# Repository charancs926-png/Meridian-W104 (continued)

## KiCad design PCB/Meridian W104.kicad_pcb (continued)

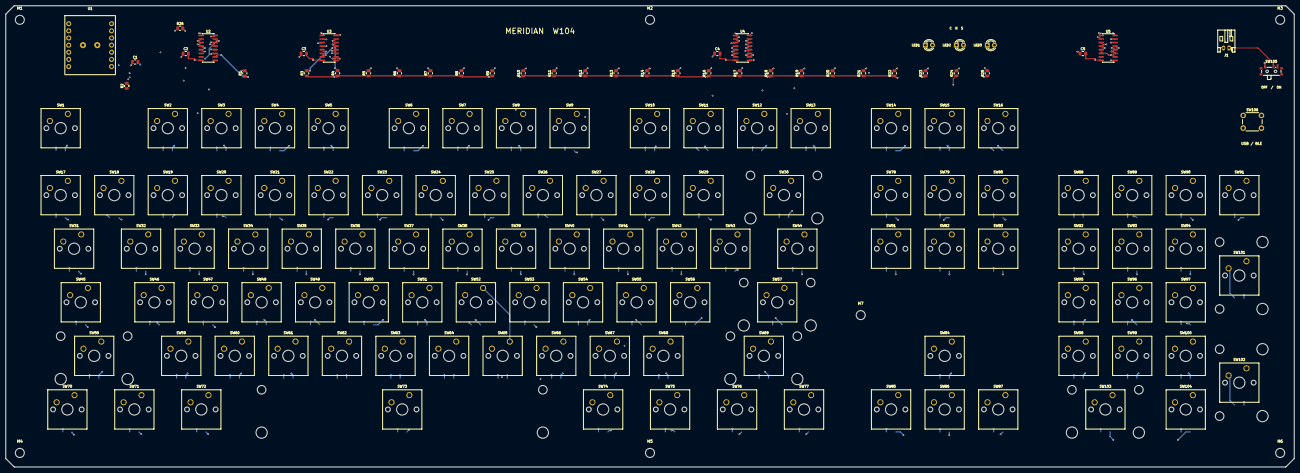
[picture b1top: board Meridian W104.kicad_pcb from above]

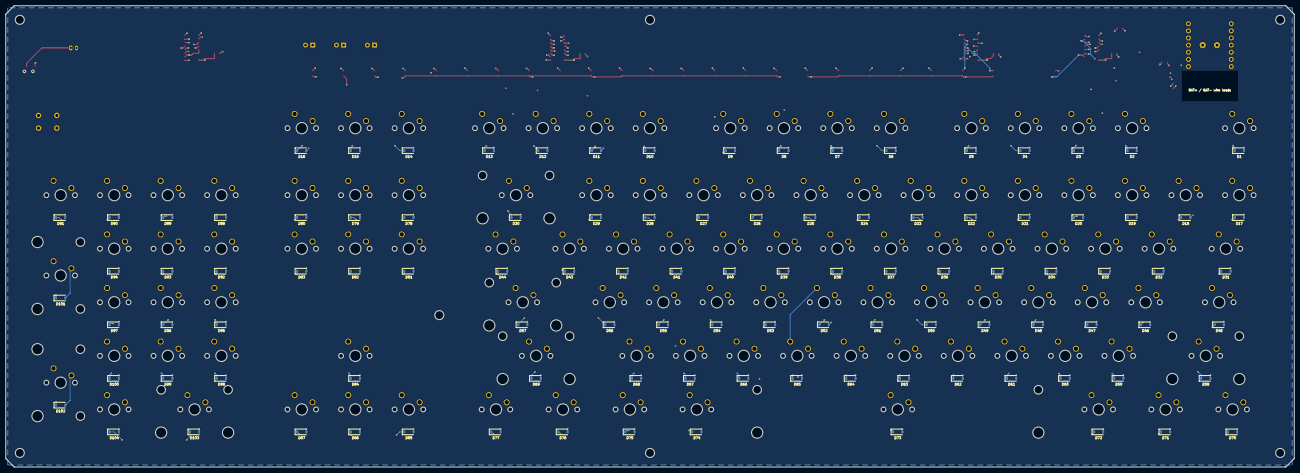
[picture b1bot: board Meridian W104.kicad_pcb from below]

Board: 4 copper layers, 458.1 x 164.0 mm, 257 parts (104 on the bottom side), 152 nets.

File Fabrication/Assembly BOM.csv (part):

Reference,Value,Footprint,Side,Technology,Notes
C1,10u / 10V,Capacitor_SMD:C_0805_2012Metric,Top,SMD,
C2,100n,Capacitor_SMD:C_0805_2012Metric,Top,SMD,
C3,100n,Capacitor_SMD:C_0805_2012Metric,Top,SMD,
C4,100n,Capacitor_SMD:C_0805_2012Metric,Top,SMD,
C5,100n,Capacitor_SMD:C_0805_2012Metric,Top,SMD,
D1,1N4148W,Diode_SMD:D_SOD-123,Bottom,SMD,
D10,1N4148W,Diode_SMD:D_SOD-123,Bottom,SMD,
D100,1N4148W,Diode_SMD:D_SOD-123,Bottom,SMD,
D101,1N4148W,Diode_SMD:D_SOD-123,Bottom,SMD,
D102,1N4148W,Diode_SMD:D_SOD-123,Bottom,SMD,
D103,1N4148W,Diode_SMD:D_SOD-123,Bottom,SMD,
D104,1N4148W,Diode_SMD:D_SOD-123,Bottom,SMD,
D11,1N4148W,Diode_SMD:D_SOD-123,Bottom,SMD,
D12,1N4148W,Diode_SMD:D_SOD-123,Bottom,SMD,
D13,1N4148W,Diode_SMD:D_SOD-123,Bottom,SMD,
D14,1N4148W,Diode_SMD:D_SOD-123,Bottom,SMD,
D15,1N4148W,Diode_SMD:D_SOD-123,Bottom,SMD,
D16,1N4148W,Diode_SMD:D_SOD-123,Bottom,SMD,
D17,1N4148W,Diode_SMD:D_SOD-123,Bottom,SMD,
D18,1N4148W,Diode_SMD:D_SOD-123,Bottom,SMD,
D19,1N4148W,Diode_SMD:D_SOD-123,Bottom,SMD,
D2,1N4148W,Diode_SMD:D_SOD-123,Bottom,SMD,
D20,1N4148W,Diode_SMD:D_SOD-123,Bottom,SMD,
D21,1N4148W,Diode_SMD:D_SOD-123,Bottom,SMD,
D22,1N4148W,Diode_SMD:D_SOD-123,Bottom,SMD,
D23,1N4148W,Diode_SMD:D_SOD-123,Bottom,SMD,
D24,1N4148W,Diode_SMD:D_SOD-123,Bottom,SMD,
D25,1N4148W,Diode_SMD:D_SOD-123,Bottom,SMD,
D26,1N4148W,Diode_SMD:D_SOD-123,Bottom,SMD,
D27,1N4148W,Diode_SMD:D_SOD-123,Bottom,SMD,
D28,1N4148W,Diode_SMD:D_SOD-123,Bottom,SMD,
D29,1N4148W,Diode_SMD:D_SOD-123,Bottom,SMD,
D3,1N4148W,Diode_SMD:D_SOD-123,Bottom,SMD,
D30,1N4148W,Diode_SMD:D_SOD-123,Bottom,SMD,
D31,1N4148W,Diode_SMD:D_SOD-123,Bottom,SMD,
D32,1N4148W,Diode_SMD:D_SOD-123,Bottom,SMD,
D33,1N4148W,Diode_SMD:D_SOD-123,Bottom,SMD,
D34,1N4148W,Diode_SMD:D_SOD-123,Bottom,SMD,
D35,1N4148W,Diode_SMD:D_SOD-123,Bottom,SMD,
D36,1N4148W,Diode_SMD:D_SOD-123,Bottom,SMD,
D37,1N4148W,Diode_SMD:D_SOD-123,Bottom,SMD,
D38,1N4148W,Diode_SMD:D_SOD-123,Bottom,SMD,
D39,1N4148W,Diode_SMD:D_SOD-123,Bottom,SMD,
D4,1N4148W,Diode_SMD:D_SOD-123,Bottom,SMD,
D40,1N4148W,Diode_SMD:D_SOD-123,Bottom,SMD,
D41,1N4148W,Diode_SMD:D_SOD-123,Bottom,SMD,
D42,1N4148W,Diode_SMD:D_SOD-123,Bottom,SMD,
D43,1N4148W,Diode_SMD:D_SOD-123,Bottom,SMD,
D44,1N4148W,Diode_SMD:D_SOD-123,Bottom,SMD,
D45,1N4148W,Diode_SMD:D_SOD-123,Bottom,SMD,
D46,1N4148W,Diode_SMD:D_SOD-123,Bottom,SMD,
D47,1N4148W,Diode_SMD:D_SOD-123,Bottom,SMD,
D48,1N4148W,Diode_SMD:D_SOD-123,Bottom,SMD,
D49,1N4148W,Diode_SMD:D_SOD-123,Bottom,SMD,
D5,1N4148W,Diode_SMD:D_SOD-123,Bottom,SMD,
D50,1N4148W,Diode_SMD:D_SOD-123,Bottom,SMD,
D51,1N4148W,Diode_SMD:D_SOD-123,Bottom,SMD,
D52,1N4148W,Diode_SMD:D_SOD-123,Bottom,SMD,
D53,1N4148W,Diode_SMD:D_SOD-123,Bottom,SMD,
D54,1N4148W,Diode_SMD:D_SOD-123,Bottom,SMD,
D55,1N4148W,Diode_SMD:D_SOD-123,Bottom,SMD,
D56,1N4148W,Diode_SMD:D_SOD-123,Bottom,SMD,
D57,1N4148W,Diode_SMD:D_SOD-123,Bottom,SMD,
D58,1N4148W,Diode_SMD:D_SOD-123,Bottom,SMD,
D59,1N4148W,Diode_SMD:D_SOD-123,Bottom,SMD,
D6,1N4148W,Diode_SMD:D_SOD-123,Bottom,SMD,
D60,1N4148W,Diode_SMD:D_SOD-123,Bottom,SMD,
D61,1N4148W,Diode_SMD:D_SOD-123,Bottom,SMD,
D62,1N4148W,Diode_SMD:D_SOD-123,Bottom,SMD,
D63,1N4148W,Diode_SMD:D_SOD-123,Bottom,SMD,
D64,1N4148W,Diode_SMD:D_SOD-123,Bottom,SMD,
D65,1N4148W,Diode_SMD:D_SOD-123,Bottom,SMD,
D66,1N4148W,Diode_SMD:D_SOD-123,Bottom,SMD,
D67,1N4148W,Diode_SMD:D_SOD-123,Bottom,SMD,
D68,1N4148W,Diode_SMD:D_SOD-123,Bottom,SMD,
D69,1N4148W,Diode_SMD:D_SOD-123,Bottom,SMD,
D7,1N4148W,Diode_SMD:D_SOD-123,Bottom,SMD,
D70,1N4148W,Diode_SMD:D_SOD-123,Bottom,SMD,
D71,1N4148W,Diode_SMD:D_SOD-123,Bottom,SMD,
D72,1N4148W,Diode_SMD:D_SOD-123,Bottom,SMD,
D73,1N4148W,Diode_SMD:D_SOD-123,Bottom,SMD,
D74,1N4148W,Diode_SMD:D_SOD-123,Bottom,SMD,
D75,1N4148W,Diode_SMD:D_SOD-123,Bottom,SMD,
D76,1N4148W,Diode_SMD:D_SOD-123,Bottom,SMD,
D77,1N4148W,Diode_SMD:D_SOD-123,Bottom,SMD,
D78,1N4148W,Diode_SMD:D_SOD-123,Bottom,SMD,
D79,1N4148W,Diode_SMD:D_SOD-123,Bottom,SMD,
D8,1N4148W,Diode_SMD:D_SOD-123,Bottom,SMD,
D80,1N4148W,Diode_SMD:D_SOD-123,Bottom,SMD,
D81,1N4148W,Diode_SMD:D_SOD-123,Bottom,SMD,
D82,1N4148W,Diode_SMD:D_SOD-123,Bottom,SMD,
D83,1N4148W,Diode_SMD:D_SOD-123,Bottom,SMD,
D84,1N4148W,Diode_SMD:D_SOD-123,Bottom,SMD,
D85,1N4148W,Diode_SMD:D_SOD-123,Bottom,SMD,
D86,1N4148W,Diode_SMD:D_SOD-123,Bottom,SMD,
D87,1N4148W,Diode_SMD:D_SOD-123,Bottom,SMD,
D88,1N4148W,Diode_SMD:D_SOD-123,Bottom,SMD,
D89,1N4148W,Diode_SMD:D_SOD-123,Bottom,SMD,
D9,1N4148W,Diode_SMD:D_SOD-123,Bottom,SMD,
D90,1N4148W,Diode_SMD:D_SOD-123,Bottom,SMD,
D91,1N4148W,Diode_SMD:D_SOD-123,Bottom,SMD,
D92,1N4148W,Diode_SMD:D_SOD-123,Bottom,SMD,
D93,1N4148W,Diode_SMD:D_SOD-123,Bottom,SMD,
D94,1N4148W,Diode_SMD:D_SOD-123,Bottom,SMD,
D95,1N4148W,Diode_SMD:D_SOD-123,Bottom,SMD,
D96,1N4148W,Diode_SMD:D_SOD-123,Bottom,SMD,
D97,1N4148W,Diode_SMD:D_SOD-123,Bottom,SMD,
D98,1N4148W,Diode_SMD:D_SOD-123,Bottom,SMD,
D99,1N4148W,Diode_SMD:D_SOD-123,Bottom,SMD,
J1,Protected 1S LiPo,Connector_JST:JST_PH_S2B-PH-K_1x02_P2.00mm_Horizontal,Top,THT,
LED1,CAPS,LED_THT:LED_D3.0mm,Top,THT,
LED2,NUM,LED_THT:LED_D3.0mm,Top,THT,
LED3,SCROLL,LED_THT:LED_D3.0mm,Top,THT,
R1,22k,Resistor_SMD:R_0805_2012Metric,Top,SMD,
R10,22k,Resistor_SMD:R_0805_2012Metric,Top,SMD,
R11,22k,Resistor_SMD:R_0805_2012Metric,Top,SMD,
R12,22k,Resistor_SMD:R_0805_2012Metric,Top,SMD,
R13,22k,Resistor_SMD:R_0805_2012Metric,Top,SMD,
R14,22k,Resistor_SMD:R_0805_2012Metric,Top,SMD,
R15,22k,Resistor_SMD:R_0805_2012Metric,Top,SMD,
R16,22k,Resistor_SMD:R_0805_2012Metric,Top,SMD,
R17,22k,Resistor_SMD:R_0805_2012Metric,Top,SMD,
R18,22k,Resistor_SMD:R_0805_2012Metric,Top,SMD,
R19,22k,Resistor_SMD:R_0805_2012Metric,Top,SMD,
R2,22k,Resistor_SMD:R_0805_2012Metric,Top,SMD,
R20,22k,Resistor_SMD:R_0805_2012Metric,Top,SMD,
R21,22k,Resistor_SMD:R_0805_2012Metric,Top,SMD,
R22,22k,Resistor_SMD:R_0805_2012Metric,Top,SMD,
R23,1k,Resistor_SMD:R_0805_2012Metric,Top,SMD,
R24,1k,Resistor_SMD:R_0805_2012Metric,Top,SMD,
R25,1k,Resistor_SMD:R_0805_2012Metric,Top,SMD,
R26,100k / OE off,Resistor_SMD:R_0805_2012Metric,Top,SMD,
R3,22k,Resistor_SMD:R_0805_2012Metric,Top,SMD,
R4,22k,Resistor_SMD:R_0805_2012Metric,Top,SMD,
R5,22k,Resistor_SMD:R_0805_2012Metric,Top,SMD,
R6,22k,Resistor_SMD:R_0805_2012Metric,Top,SMD,
R7,22k,Resistor_SMD:R_0805_2012Metric,Top,SMD,
R8,22k,Resistor_SMD:R_0805_2012Metric,Top,SMD,
R9,22k,Resistor_SMD:R_0805_2012Metric,Top,SMD,
SW1,1u,Button_Switch_Keyboard:SW_Cherry_MX_1.00u_PCB,Top,THT,"Soldered MX PCB switches, not hot-swap."
SW10,1u,Button_Switch_Keyboard:SW_Cherry_MX_1.00u_PCB,Top,THT,"Soldered MX PCB switches, not hot-swap."
SW100,1u,Button_Switch_Keyboard:SW_Cherry_MX_1.00u_PCB,Top,THT,"Soldered MX PCB switches, not hot-swap."
SW101,1u,Button_Switch_Keyboard:SW_Cherry_MX_2.00u_Vertical_PCB,Top,THT,"Soldered MX PCB switches, not hot-swap."
SW102,1u,Button_Switch_Keyboard:SW_Cherry_MX_2.00u_Vertical_PCB,Top,THT,"Soldered MX PCB switches, not hot-swap."
SW103,2u,Button_Switch_Keyboard:SW_Cherry_MX_2.00u_PCB,Top,THT,"Soldered MX PCB switches, not hot-swap."
SW104,1u,Button_Switch_Keyboard:SW_Cherry_MX_1.00u_PCB,Top,THT,"Soldered MX PCB switches, not hot-swap."
SW105,BATTERY ON / OFF,Button_Switch_SMD:SW_SPDT_PCM12,Top,SMD,
SW106,USB / BLE toggle,Button_Switch_THT:SW_PUSH_6mm,Top,THT,
SW11,1u,Button_Switch_Keyboard:SW_Cherry_MX_1.00u_PCB,Top,THT,"Soldered MX PCB switches, not hot-swap."
SW12,1u,Button_Switch_Keyboard:SW_Cherry_MX_1.00u_PCB,Top,THT,"Soldered MX PCB switches, not hot-swap."
SW13,1u,Button_Switch_Keyboard:SW_Cherry_MX_1.00u_PCB,Top,THT,"Soldered MX PCB switches, not hot-swap."
SW14,1u,Button_Switch_Keyboard:SW_Cherry_MX_1.00u_PCB,Top,THT,"Soldered MX PCB switches, not hot-swap."
SW15,1u,Button_Switch_Keyboard:SW_Cherry_MX_1.00u_PCB,Top,THT,"Soldered MX PCB switches, not hot-swap."
SW16,1u,Button_Switch_Keyboard:SW_Cherry_MX_1.00u_PCB,Top,THT,"Soldered MX PCB switches, not hot-swap."
SW17,1u,Button_Switch_Keyboard:SW_Cherry_MX_1.00u_PCB,Top,THT,"Soldered MX PCB switches, not hot-swap."
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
